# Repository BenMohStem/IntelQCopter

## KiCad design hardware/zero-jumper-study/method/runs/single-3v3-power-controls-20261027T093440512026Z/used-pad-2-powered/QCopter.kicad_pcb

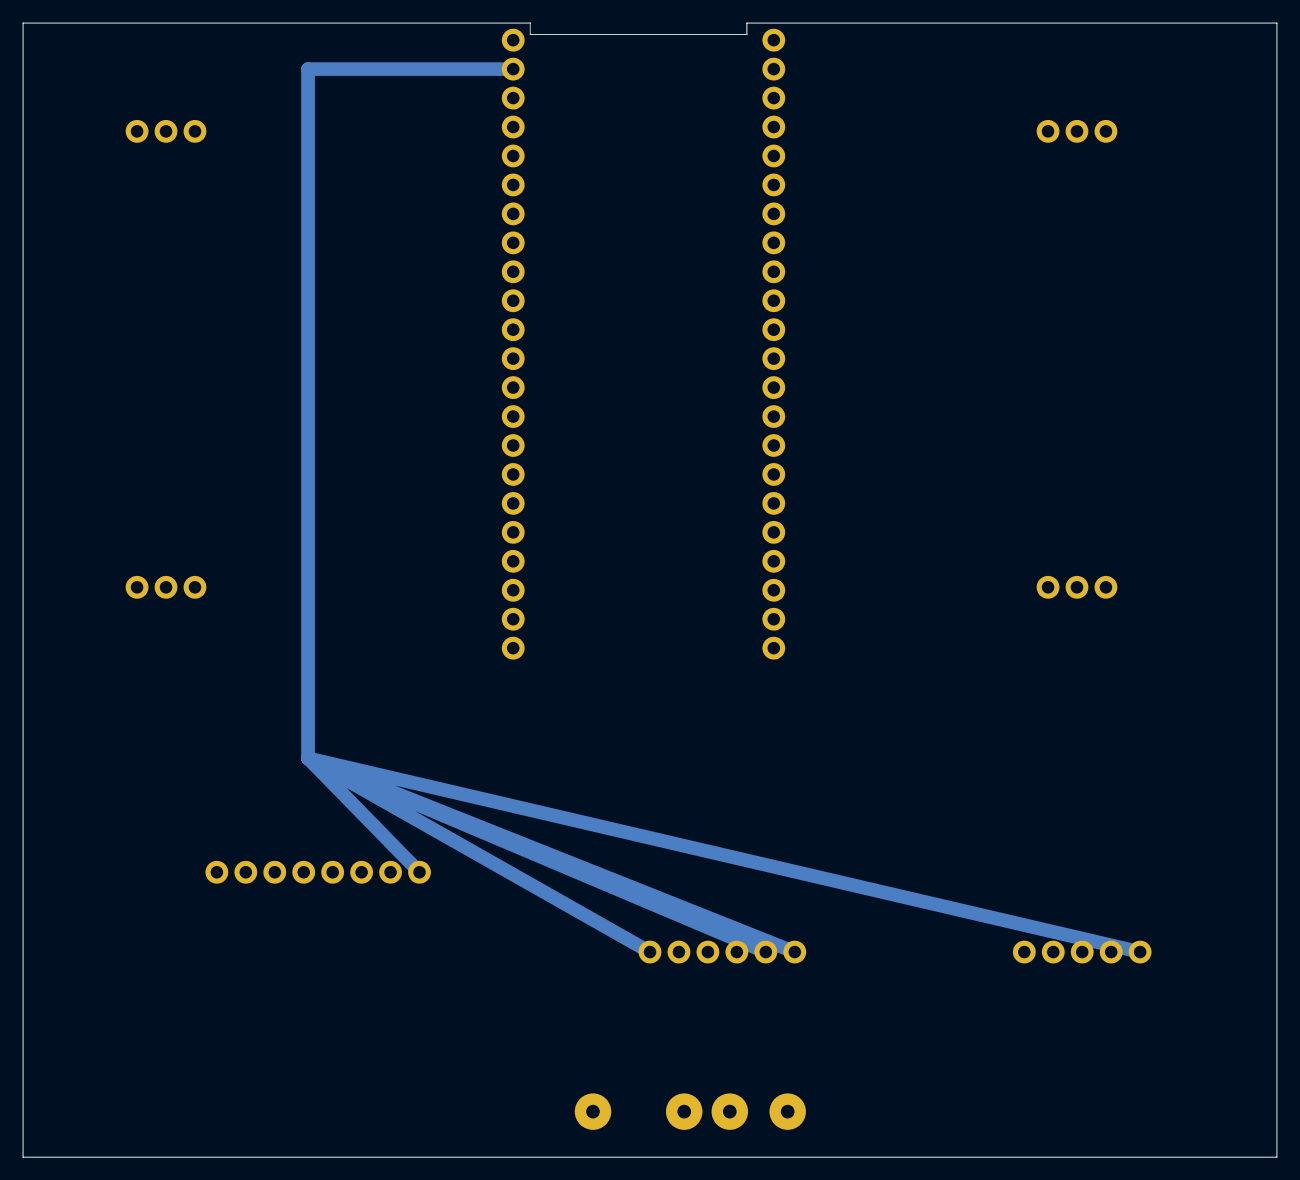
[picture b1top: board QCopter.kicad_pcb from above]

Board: 2 copper layers, 110.0 x 99.5 mm, 9 parts (0 on the bottom side), 15 nets.

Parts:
J1: LIDAR_SOLDER_WIRES; Lidar_Free_Solder_Lands
J2, J3, J4, J5: ESC_Servo_1x03
U1: ESP32_S3_DevKitC_1_44pin
U2: MPU6050_GY521_1x08
U3: BMP280_GY_1x06
U4: Magnetometer_GY271_1x05

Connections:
3V3: U1.2, U2.1, U3.1, U3.5, U3.6, U4.1
ESC1_SIGNAL: J5.3, U1.4
ESC2_SIGNAL: J2.3, U1.40
ESC3_SIGNAL: J4.3, U1.11
ESC4_SIGNAL: J3.3, U1.27
FC_5V: J1.1, J4.2, U1.21
FC_TX_TO_LIDAR: J1.4, U1.9
GND: J1.2, J2.1, J3.1, J4.1, J5.1, U1.22, U1.23, U1.24, U1.44, U2.2, U2.7, U3.2, U4.2
LIDAR_TO_FC_RX: J1.3, U1.8
MAG_DRDY: U1.38, U4.5
MPU_INT: U1.20, U2.8
MPU_SCL: U1.18, U2.3
MPU_SDA: U1.19, U2.4
SLOW_SCL: U1.37, U3.3, U4.3
SLOW_SDA: U1.36, U3.4, U4.4
